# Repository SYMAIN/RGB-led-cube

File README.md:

# RGB-led-cube

This project was created to learn more about circuit boards, electronic components, 3D printing, electricity and embedded programming. It consists of 4x4x4 RGB LEDs, each able to be turned on individually using only 6 Arduino pins by using [Shift Registers](https://en.wikipedia.org/wiki/Shift_register) and [Bit Angle Modulation](https://tiemenwaterreus.com/posts/4-bit-angle-modulating/).

Demos:

https://user-images.githubusercontent.com/73000223/192903921-adc4f65e-4e14-4fca-b12e-bf22174f0ff1.mov

https://user-images.githubusercontent.com/73000223/192928861-055b67dd-9abe-455a-9a94-8997f7c88414.mp4

Dev Notes:
[Pitch Slides](https://docs.google.com/presentation/d/1Q3SgMbCxCJnp64us6YknnfaCr0XkEVGkdK7O4LI-4xs/edit?usp=sharing)

A project inspired by Kevin Darrah on [YouTube](https://www.youtube.com/watch?v=guppB4cK3oU&list=PL0JWuCHXfJ2zXVRqFRFVq-lNt_xtCYMjx&index=5) && Malt Whiskey on [YouTube](https://www.youtube.com/watch?v=gzdSvov-5-8)

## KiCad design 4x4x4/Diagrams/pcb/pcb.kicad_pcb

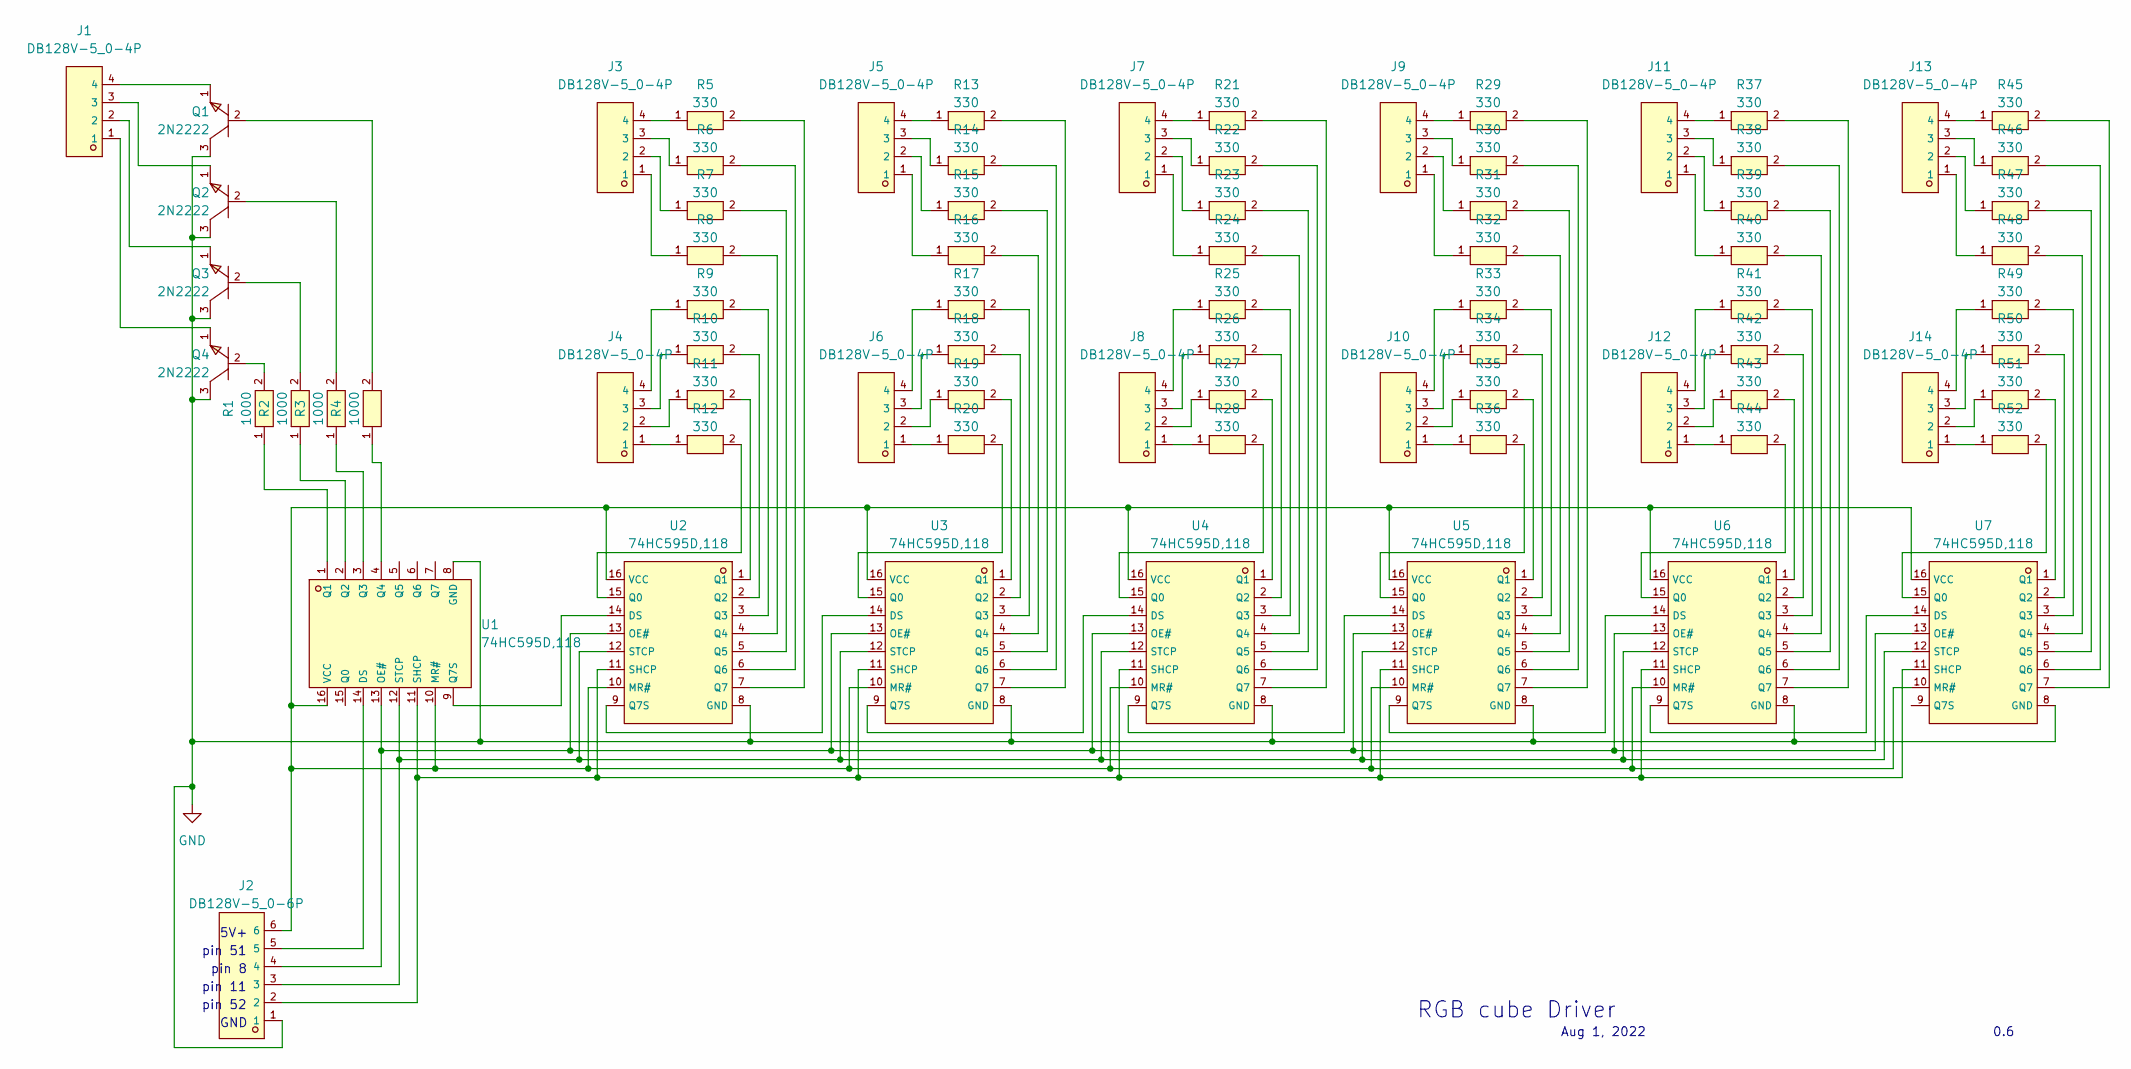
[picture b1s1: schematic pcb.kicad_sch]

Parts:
J1, J3, J4, J5, J6, J7, J8, J9, J10, J11, J12, J13, J14: DB128V-5_0-4P; CONN-TH_DB128V-5.0-4P; LCSC C424682
J2: DB128V-5_0-6P; CONN-TH_6P-P5.00_DB128V; LCSC C424686
Q1, Q2, Q3, Q4: 2N2222; TO-92-3_L4.9-W3.7-P1.27-L; LCSC C118536
R1, R2, R3, R4: 1000; RES-TH_BD2.4-L6.3-P10.30-D0.6; LCSC C433798
R5, R6, R7, R8, R9, R10, R11, R12, R13, R14, R15, R16, R17, R18, R19, R20, R21, R22, R23, R24, R25, R26, R27, R28, R29, R30, R31, R32, R33, R34, R35, R36, R37, R38, R39, R40, R41, R42, R43, R44, R45, R46, R47, R48, R49, R50, R51, R52: 330; RES-TH_BD2.4-L6.3-P10.30-D0.6; LCSC C433789
U1, U2, U3, U4, U5, U6, U7: 74HC595D,118; SOIC-16_L9.9-W3.9-P1.27-LS6.0-BL; LCSC C5947

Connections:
GND: J2.1, Q1.3 (C), Q2.3 (C), Q3.3 (C), Q4.3 (C), U1.8 (GND), U2.8 (GND), U3.8 (GND), U4.8 (GND), U5.8 (GND), U6.8 (GND), U7.8 (GND)
unnamed: J1.1, Q4.1 (E)
unnamed: J1.2, Q3.1 (E)
unnamed: J1.3, Q2.1 (E)
unnamed: J1.4, Q1.1 (E)
unnamed: J2.2, U1.11 (SHCP), U2.11 (SHCP), U3.11 (SHCP), U4.11 (SHCP), U5.11 (SHCP), U6.11 (SHCP), U7.11 (SHCP)
unnamed: J2.3, U1.12 (STCP), U2.12 (STCP), U3.12 (STCP), U4.12 (STCP), U5.12 (STCP), U6.12 (STCP), U7.12 (STCP)
unnamed: J2.4, U1.13 (OE#), U2.13 (OE#), U3.13 (OE#), U4.13 (OE#), U5.13 (OE#), U6.13 (OE#), U7.13 (OE#)
unnamed: J2.5, U1.14 (DS)
unnamed: J2.6, U1.10 (MR#), U1.16 (VCC), U2.10 (MR#), U2.16 (VCC), U3.10 (MR#), U3.16 (VCC), U4.10 (MR#), U4.16 (VCC), U5.10 (MR#), U5.16 (VCC), U6.10 (MR#), U6.16 (VCC), U7.10 (MR#), U7.16 (VCC)
unnamed: J3.1, R8.1
unnamed: J3.2, R7.1
unnamed: J3.3, R6.1
unnamed: J3.4, R5.1
unnamed: J4.1, R12.1
unnamed: J4.2, R11.1
unnamed: J4.3, R10.1
unnamed: J4.4, R9.1
unnamed: J5.1, R16.1
unnamed: J5.2, R15.1
unnamed: J5.3, R14.1
unnamed: J5.4, R13.1
unnamed: J6.1, R20.1
unnamed: J6.2, R19.1
unnamed: J6.3, R18.1
unnamed: J6.4, R17.1
unnamed: J7.1, R24.1
unnamed: J7.2, R23.1
unnamed: J7.3, R22.1
unnamed: J7.4, R21.1
unnamed: J8.1, R28.1
unnamed: J8.2, R27.1
unnamed: J8.3, R26.1
unnamed: J8.4, R25.1
unnamed: J9.1, R32.1
unnamed: J9.2, R31.1
unnamed: J9.3, R30.1
unnamed: J9.4, R29.1
unnamed: J10.1, R36.1
unnamed: J10.2, R35.1
unnamed: J10.3, R34.1
unnamed: J10.4, R33.1
unnamed: J11.1, R40.1
unnamed: J11.2, R39.1
unnamed: J11.3, R38.1
unnamed: J11.4, R37.1
unnamed: J12.1, R44.1
unnamed: J12.2, R43.1
unnamed: J12.3, R42.1
unnamed: J12.4, R41.1
unnamed: J13.1, R48.1
unnamed: J13.2, R47.1
unnamed: J13.3, R46.1
unnamed: J13.4, R45.1
unnamed: J14.1, R52.1
unnamed: J14.2, R51.1
unnamed: J14.3, R50.1
unnamed: J14.4, R49.1
unnamed: Q1.2 (B), R4.2
unnamed: Q2.2 (B), R3.2
unnamed: Q3.2 (B), R2.2
unnamed: Q4.2 (B), R1.2
unnamed: R1.1, U1.1 (Q1)
unnamed: R2.1, U1.2 (Q2)
unnamed: R3.1, U1.3 (Q3)
unnamed: R4.1, U1.4 (Q4)
unnamed: R5.2, U2.7 (Q7)
unnamed: R6.2, U2.6 (Q6)
unnamed: R7.2, U2.5 (Q5)
unnamed: R8.2, U2.4 (Q4)
unnamed: R9.2, U2.3 (Q3)
unnamed: R10.2, U2.2 (Q2)
unnamed: R11.2, U2.1 (Q1)
unnamed: R12.2, U2.15 (Q0)
unnamed: R13.2, U3.7 (Q7)
unnamed: R14.2, U3.6 (Q6)
unnamed: R15.2, U3.5 (Q5)
unnamed: R16.2, U3.4 (Q4)
unnamed: R17.2, U3.3 (Q3)
unnamed: R18.2, U3.2 (Q2)
unnamed: R19.2, U3.1 (Q1)
unnamed: R20.2, U3.15 (Q0)
unnamed: R21.2, U4.7 (Q7)
unnamed: R22.2, U4.6 (Q6)
unnamed: R23.2, U4.5 (Q5)
unnamed: R24.2, U4.4 (Q4)
unnamed: R25.2, U4.3 (Q3)
unnamed: R26.2, U4.2 (Q2)
unnamed: R27.2, U4.1 (Q1)
unnamed: R28.2, U4.15 (Q0)
unnamed: R29.2, U5.7 (Q7)
unnamed: R30.2, U5.6 (Q6)
unnamed: R31.2, U5.5 (Q5)
unnamed: R32.2, U5.4 (Q4)
unnamed: R33.2, U5.3 (Q3)
unnamed: R34.2, U5.2 (Q2)
unnamed: R35.2, U5.1 (Q1)
unnamed: R36.2, U5.15 (Q0)
unnamed: R37.2, U6.7 (Q7)
unnamed: R38.2, U6.6 (Q6)
unnamed: R39.2, U6.5 (Q5)
unnamed: R40.2, U6.4 (Q4)
unnamed: R41.2, U6.3 (Q3)
unnamed: R42.2, U6.2 (Q2)
unnamed: R43.2, U6.1 (Q1)
unnamed: R44.2, U6.15 (Q0)
unnamed: R45.2, U7.7 (Q7)
unnamed: R46.2, U7.6 (Q6)
unnamed: R47.2, U7.5 (Q5)
unnamed: R48.2, U7.4 (Q4)
unnamed: R49.2, U7.3 (Q3)
unnamed: R50.2, U7.2 (Q2)
unnamed: R51.2, U7.1 (Q1)
unnamed: R52.2, U7.15 (Q0)
unnamed: U1.9 (Q7S), U2.14 (DS)
unnamed: U2.9 (Q7S), U3.14 (DS)
unnamed: U3.9 (Q7S), U4.14 (DS)
unnamed: U4.9 (Q7S), U5.14 (DS)
unnamed: U5.9 (Q7S), U6.14 (DS)
unnamed: U6.9 (Q7S), U7.14 (DS)

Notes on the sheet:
RGB cube Driver
Aug 1, 2022
pin 52
0.6
pin 11
GND
5V+
pin 8
pin 51

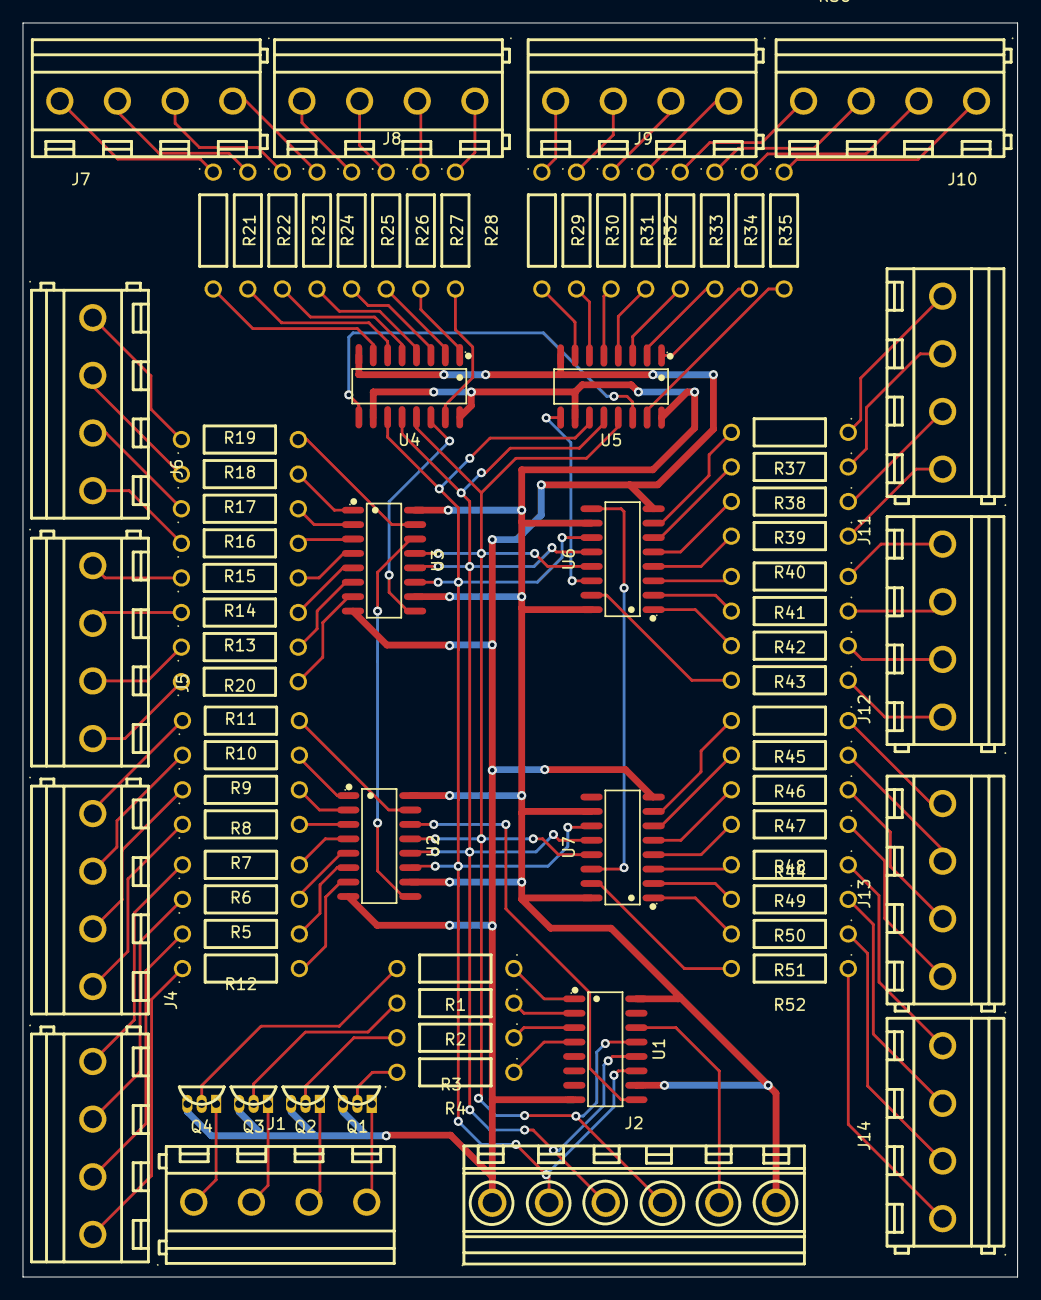
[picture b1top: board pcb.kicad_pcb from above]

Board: 2 copper layers, 87.6 x 110.5 mm, 77 parts (0 on the bottom side), 120 nets.

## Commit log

2021-12-21 added demo code
2021-12-24 multiplexing
2022-01-02 add night rider
2022-01-03 add BAM
2022-01-03 change clock/data pins to work with SPI
2022-01-03 add basic boilerplate code
2022-01-03 Timer is function, basic BAM outlined
2022-01-03 add SPI tester, it doesnt work
2022-01-03 add registers testing
2022-01-09 registers a-ok
2022-01-09 output registers modified, working
2022-01-09 SPI fixed, don't plug in wires into the wrong pins! No software changes.
2022-01-10 before rewrite of timer function
2022-01-10 BAM functional
2022-01-10 night BAMmer
2022-01-12 before revert
2022-01-12 add notable LED commands for later study
2022-01-13 add blanking. No major software changes. Remember that LEDs have different resistances!
2022-01-13 change timer
2022-01-20 init 4x4x4
2022-01-20 created stack
2022-01-20 patch new 4x4x4 code to work
2022-01-20 change data shifting order to work with our circuit
2022-01-20 minor changes
2022-01-22 add anode info
2022-01-23 stack
2022-01-23 modify anis
2022-01-23 resolve pins
2022-01-23 change allOn() animations
2022-01-23 disable other animations temporarily for debugging
2022-01-23 only blue
2022-01-23 trying hardcoding for debugging
2022-01-23 undo brute fore
2022-01-23 undo brute force
2022-01-23 mirror first level across all levels
2022-01-23 add debugging
2022-01-23 find defectinve red call
2022-01-23 change anode config
2022-01-23 check RGB arrays
2022-01-23 check all blue layers
2022-01-23 add shifting loggin
2022-01-23 debug BAM loops
2022-01-23 clarify each data set
2022-01-23 check blue0 byte array
2022-01-23 check formula output
2022-01-23 testing data inside vs outside timer
2022-01-23 remove unspecific bools
2022-01-23 rm LED calls
2022-01-23 verify that data is finished setting before doing timer stuffs
2022-01-23 forgot brackets around for loop
2022-01-23 brute force
2022-01-23 mirror the anode pattern just in case
2022-01-23 remove duplicate pinMode(blankPin, OUTPUT) call
2022-01-24 resolve color pin
2022-01-24 add uno code
2022-01-25 minimize chances of errors on Main
2022-01-25 all on
2022-01-25 all red
2022-01-25 disable register hacks
2022-01-25 change to red
2022-01-25 green
2022-01-25 real BAM
2022-01-25 real blue
2022-01-25 del old code
2022-01-25 add color functions
2022-01-25 resolve color
2022-01-25 fix blue function
2022-01-25 resolve
2022-01-25 add missle animation
2022-01-25 fix LED multiple issues
2022-01-25 revert timer
2022-01-25 resolve files
2022-01-25 multiple LEDs fixed
2022-01-25 add fireworks animation
2022-01-25 add tracer animation
2022-01-25 revert to working code
2022-01-25 add part of sparkles() animation back
2022-01-25 readd fireworks and tracer
2022-01-25 order issue
2022-01-25 quicken fireworks
2022-01-25 add error handling to LED
2022-01-25 change brightness of firework
2022-01-25 add delay in between fireworks
2022-01-25 get animations ready to integrate with button
2022-01-26 set to fireworks animations
2022-01-26 add LED function comment
2022-01-26 clean up code
2022-01-26 button working
2022-06-28 added diagrams
2022-06-28 resolve merge issue
2022-06-28 rearranged files
2022-06-29 fixed diamgram quad 1 wiring
2022-06-29 connected latch and clock wires in diagram
2022-06-29 Finished quad 2-3
2022-06-29 created 4x4x4 pcb
2022-07-01 revised quad 1 diagram
2022-07-01 add breaker schematic
2022-07-01 minor change
2022-07-02 start nano test code
2022-07-03 add mostly working shift register code
2022-07-03 add functioning SPI code
2022-07-03 add small readme
2022-07-03 fix readme
2022-07-03 fix readme #2
2022-07-04 add 8x8x8 BAM code. Compiles, untested.
2022-07-05 Add sample AC switch. Start DC transistor switch.
2022-07-05 add some components to AC breaker circuit
2022-07-07 laying out 3d model of pcb
2022-07-07 add prototype convertor circuit
2022-07-07 fix small mistake
2022-07-08 finish general layout for pcb
2022-07-12 small correction to dc-
2022-07-12 layout pcb complete
2022-07-27 add final 4x4x4 pcb
2022-07-27 review pcb
2022-07-27 fix? pcb
2022-07-27 reroute some wires
2022-07-28 fix all DRC errors
2022-07-28 cleanup tracks/vias
2022-07-28 create gerber files
2022-07-28 git add .
2022-07-28 fixed wired connection pcb
2022-08-02 changed pcb symbols
2022-08-02 add notes
2022-08-02 resolve file issues
2022-08-02 fix path changes
2022-08-03 redesign schematic
2022-08-08 create new board
2022-08-09 fixed diagram wires
2022-08-09 newest
2022-08-22 start AC->5VDC Circuit
2022-08-22 start AC->DC5V Circuit
2022-08-27 initial sketch finished
2023-01-03 fix small typo
